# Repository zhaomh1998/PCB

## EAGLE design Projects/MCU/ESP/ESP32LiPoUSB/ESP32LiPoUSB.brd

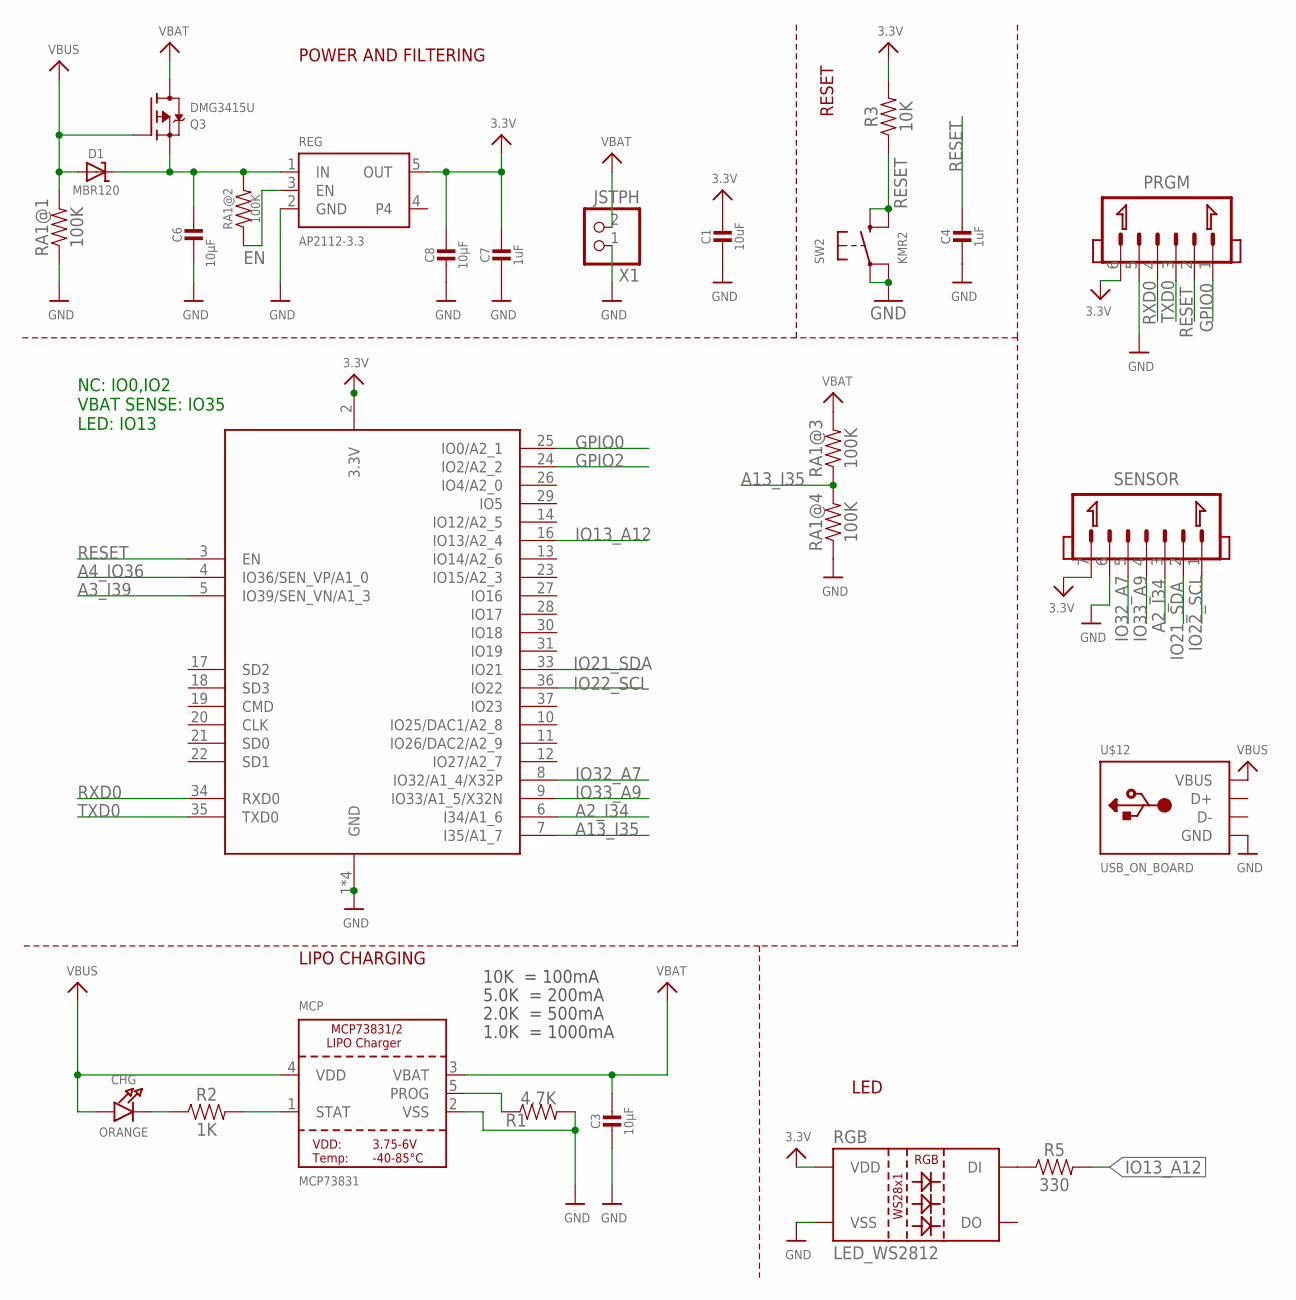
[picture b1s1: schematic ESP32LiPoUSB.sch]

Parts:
C1: 10uF; CAP_0805
C3, C8: 10µF; CAP_0805
C4, C7: 1uF; CAP_0603
C6: 10µF; CAP_0603
CHG: ORANGE; MICROBUILDER_CHIPLED_0603
D1: MBR120; SOD-123
MCP: MCP73831; SOT23-5
PRGM: JST_1.25_6P; JST1.25_6P
Q3: DMG3415U; SOT23-R
R1: 4.7K; 0603
R2: 1K; 0603
R3: 10K; 0603
R5: 330; 0603
RA1: 100K; RESCAF80P320X160X60-8N
REG: AP2112-3.3; SOT23-5
RGB: LED_WS2812; LED-TRICOLOR-5050-IC
SENSOR: JST_1.25_7P; JST1.25_7P
SW2: KMR2; BTN_KMR2_4.6X2.8
U$12: USB_ON_BOARD
X1: JSTPH; JSTPH2
X2: ESP32_WROOM32_SKINNY; WROOM32_SKINNY

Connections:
3.3V: C1.1, C7.1, C8.1, PRGM.6, R3.2, REG.5 (OUT), RGB.VDD, SENSOR.7, X2.2 (3.3V)
A2_I34: SENSOR.3, X2.6 (I34/A1_6)
A3_I39: X2.5 (IO39/SEN_VN/A1_3)
A4_IO36: X2.4 (IO36/SEN_VP/A1_0)
A13_I35: RA1.3 (1), RA1.8 (2), X2.7 (I35/A1_7)
EN: RA1.2 (1), REG.3 (EN)
GND: C1.2, C3.2, C4.2, C6.2, C7.2, C8.2, MCP.2 (VSS), PRGM.5, R1.2, RA1.1, RA1.4 (1), REG.2 (GND), RGB.VSS, SENSOR.6, SW2.A, SW2.A' (P1), U$12.GND, X1.1, X2.1 (GND), X2.15 (GND), X2.38 (GND), X2.P$1 (GND)
GPIO0: PRGM.1, X2.25 (IO0/A2_1)
GPIO2: X2.24 (IO2/A2_2)
IO13_A12: R5.2, X2.16 (IO13/A2_4)
IO21_SDA: SENSOR.2, X2.33 (IO21)
IO22_SCL: SENSOR.1, X2.36 (IO22)
IO32_A7: SENSOR.5, X2.8 (IO32/A1_4/X32P)
IO33_A9: SENSOR.4, X2.9 (IO33/A1_5/X32N)
unnamed: CHG.C, R2.1
unnamed: R5.1, RGB.DIN (DI)
unnamed: MCP.1 (STAT), R2.2
unnamed: MCP.5 (PROG), R1.1
unnamed: C6.1, D1.C, Q3.2 (S), RA1.6 (2), REG.1 (IN)
RESET: C4.1, PRGM.2, R3.1, SW2.B (S), SW2.B' (S1), X2.3 (EN)
RXD0: PRGM.4, X2.34 (RXD0)
TXD0: PRGM.3, X2.35 (TXD0)
VBAT: C3.1, MCP.3 (VBAT), Q3.3 (D), RA1.7 (2), X1.2
VBUS: CHG.A, D1.A, MCP.4 (VDD), Q3.1 (G), RA1.5 (2), U$12.VCC (VBUS)

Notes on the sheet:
POWER AND FILTERING
RESET
10K = 100mA
5.0K = 200mA
2.0K = 500mA
1.0K = 1000mA
LIPO CHARGING
LED
NC: IO0,IO2 VBAT SENSE: IO35 LED: IO13

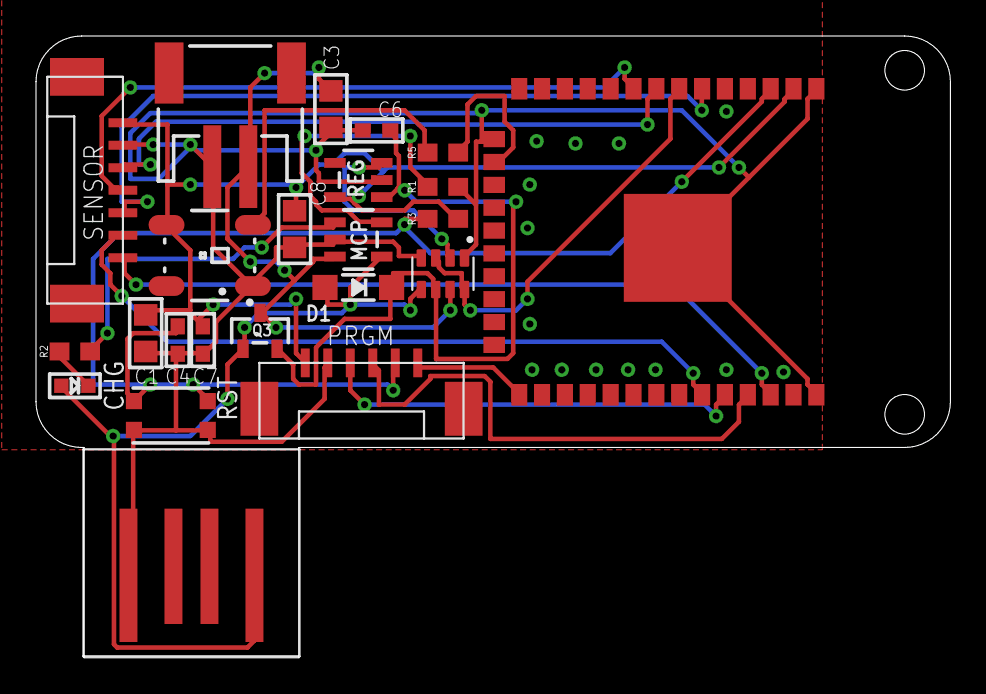
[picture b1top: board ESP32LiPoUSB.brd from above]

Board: 2 copper layers, 50.8 x 34.5 mm, 23 parts (0 on the bottom side), 21 nets.

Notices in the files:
parts and their libraries:
microbuilder: This work is placed in the public domain, and may be freely used for commercial and non-commercial work with the following conditions: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
